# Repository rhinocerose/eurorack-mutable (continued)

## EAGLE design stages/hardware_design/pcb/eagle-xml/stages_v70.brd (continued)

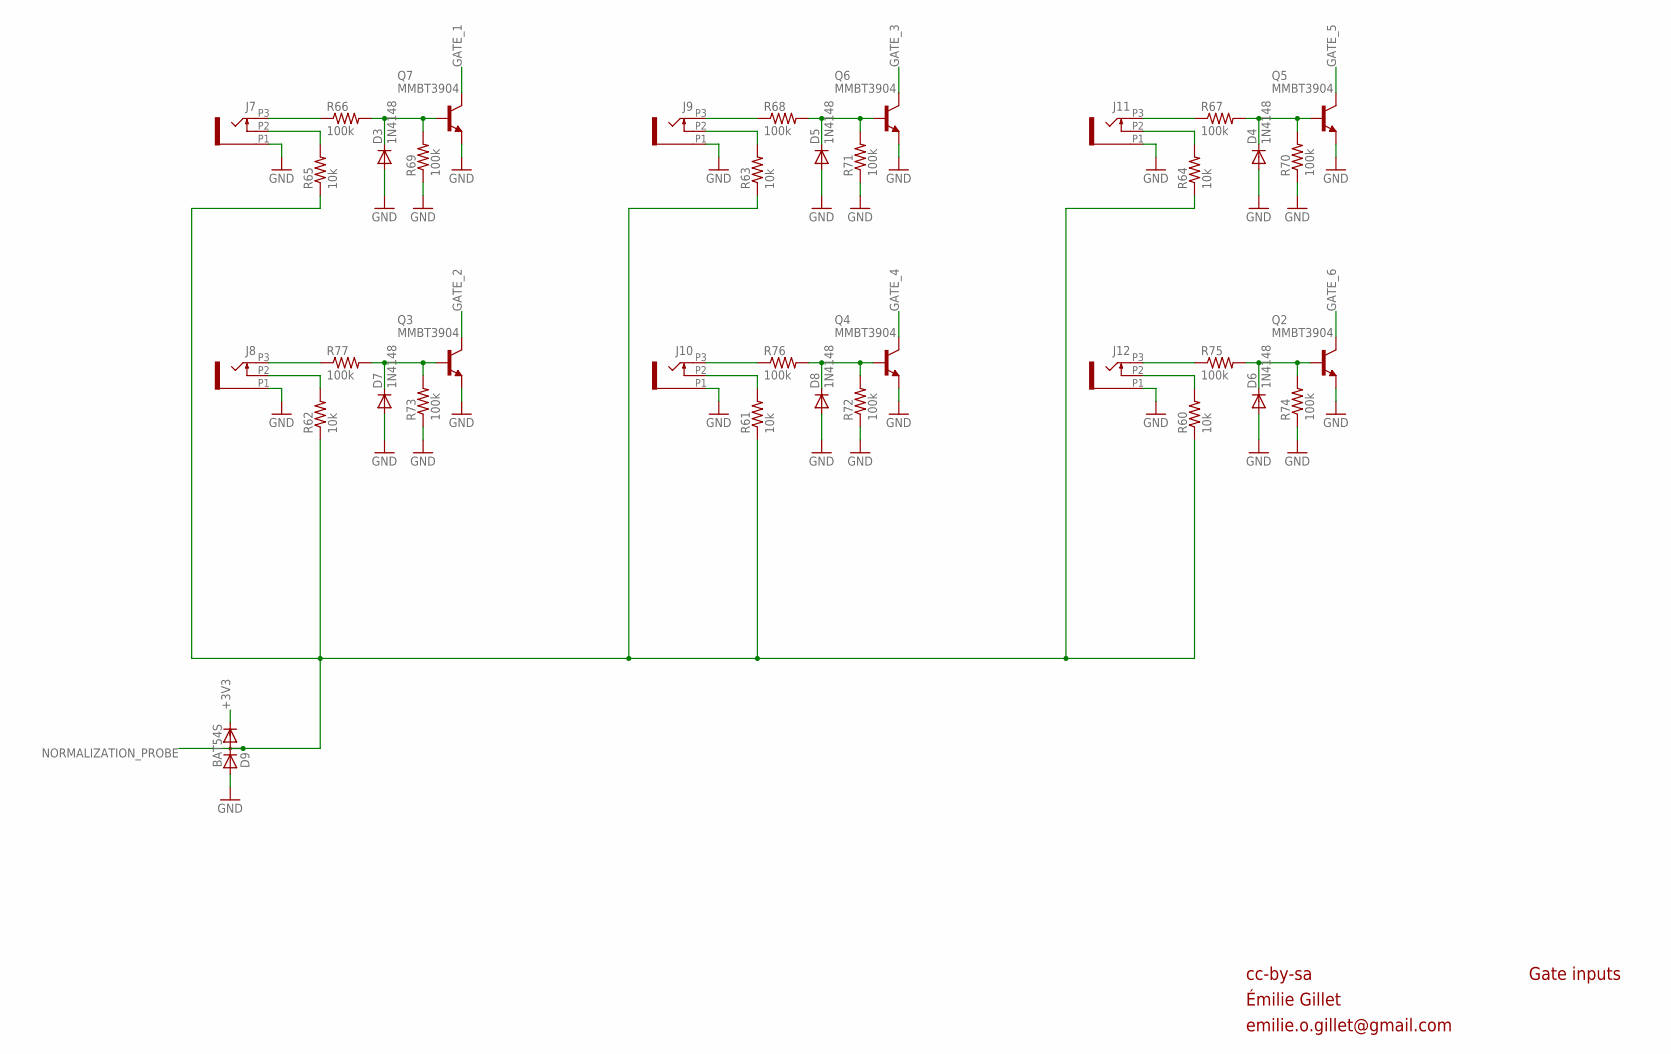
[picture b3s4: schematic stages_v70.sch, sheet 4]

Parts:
D3, D4, D5, D6, D7, D8: 1N4148; SOD523
D9: BAT54S; SOT23
J7, J8, J9, J10, J11, J12: PJ301_THONKICONN6; WQP_PJ_301M6
Q2, Q3, Q4, Q5, Q6, Q7: MMBT3904; SOT23-BEC
R60, R61, R62, R63, R64, R65: 10k; R0402
R66, R67, R68, R69, R70, R71, R72, R73, R74, R75, R76, R77: 100k; R0402

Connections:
+3V3: D9.2 (C); also elsewhere on the board
GATE_1: Q7.C; also elsewhere on the board
GATE_2: Q3.C; also elsewhere on the board
GATE_3: Q6.C; also elsewhere on the board
GATE_4: Q4.C; also elsewhere on the board
GATE_5: Q5.C; also elsewhere on the board
GATE_6: Q2.C; also elsewhere on the board
GND: D3.A, D4.A, D5.A, D6.A, D7.A, D8.A, D9.1 (A), J7.P1 (1), J8.P1 (1), J9.P1 (1), J10.P1 (1), J11.P1 (1), J12.P1 (1), Q2.E, Q3.E, Q4.E, Q5.E, Q6.E, Q7.E, R69.1, R70.1, R71.1, R72.1, R73.1, R74.1; also elsewhere on the board
unnamed: J9.P3 (3), R68.1
unnamed: J10.P3 (3), R76.1
unnamed: J10.P2 (2), R61.2
unnamed: J9.P2 (2), R63.2
unnamed: D5.C, Q6.B, R68.2, R71.2
unnamed: D8.C, Q4.B, R72.2, R76.2
unnamed: J11.P3 (3), R67.1
unnamed: J12.P3 (3), R75.1
unnamed: J12.P2 (2), R60.2
unnamed: J11.P2 (2), R64.2
unnamed: D4.C, Q5.B, R67.2, R70.2
unnamed: D6.C, Q2.B, R74.2, R75.2
unnamed: J8.P3 (3), R77.1
unnamed: J8.P2 (2), R62.2
unnamed: J7.P2 (2), R65.2
unnamed: D3.C, Q7.B, R66.2, R69.2
unnamed: D7.C, Q3.B, R73.2, R77.2
unnamed: J7.P3 (3), R66.1
NORMALIZATION_PROBE: D9.3 (AC), R60.1, R61.1, R62.1, R63.1, R64.1, R65.1; also elsewhere on the board

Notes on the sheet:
cc-by-sa
Gate inputs
Émilie Gillet
emilie.o.gillet@gmail.com

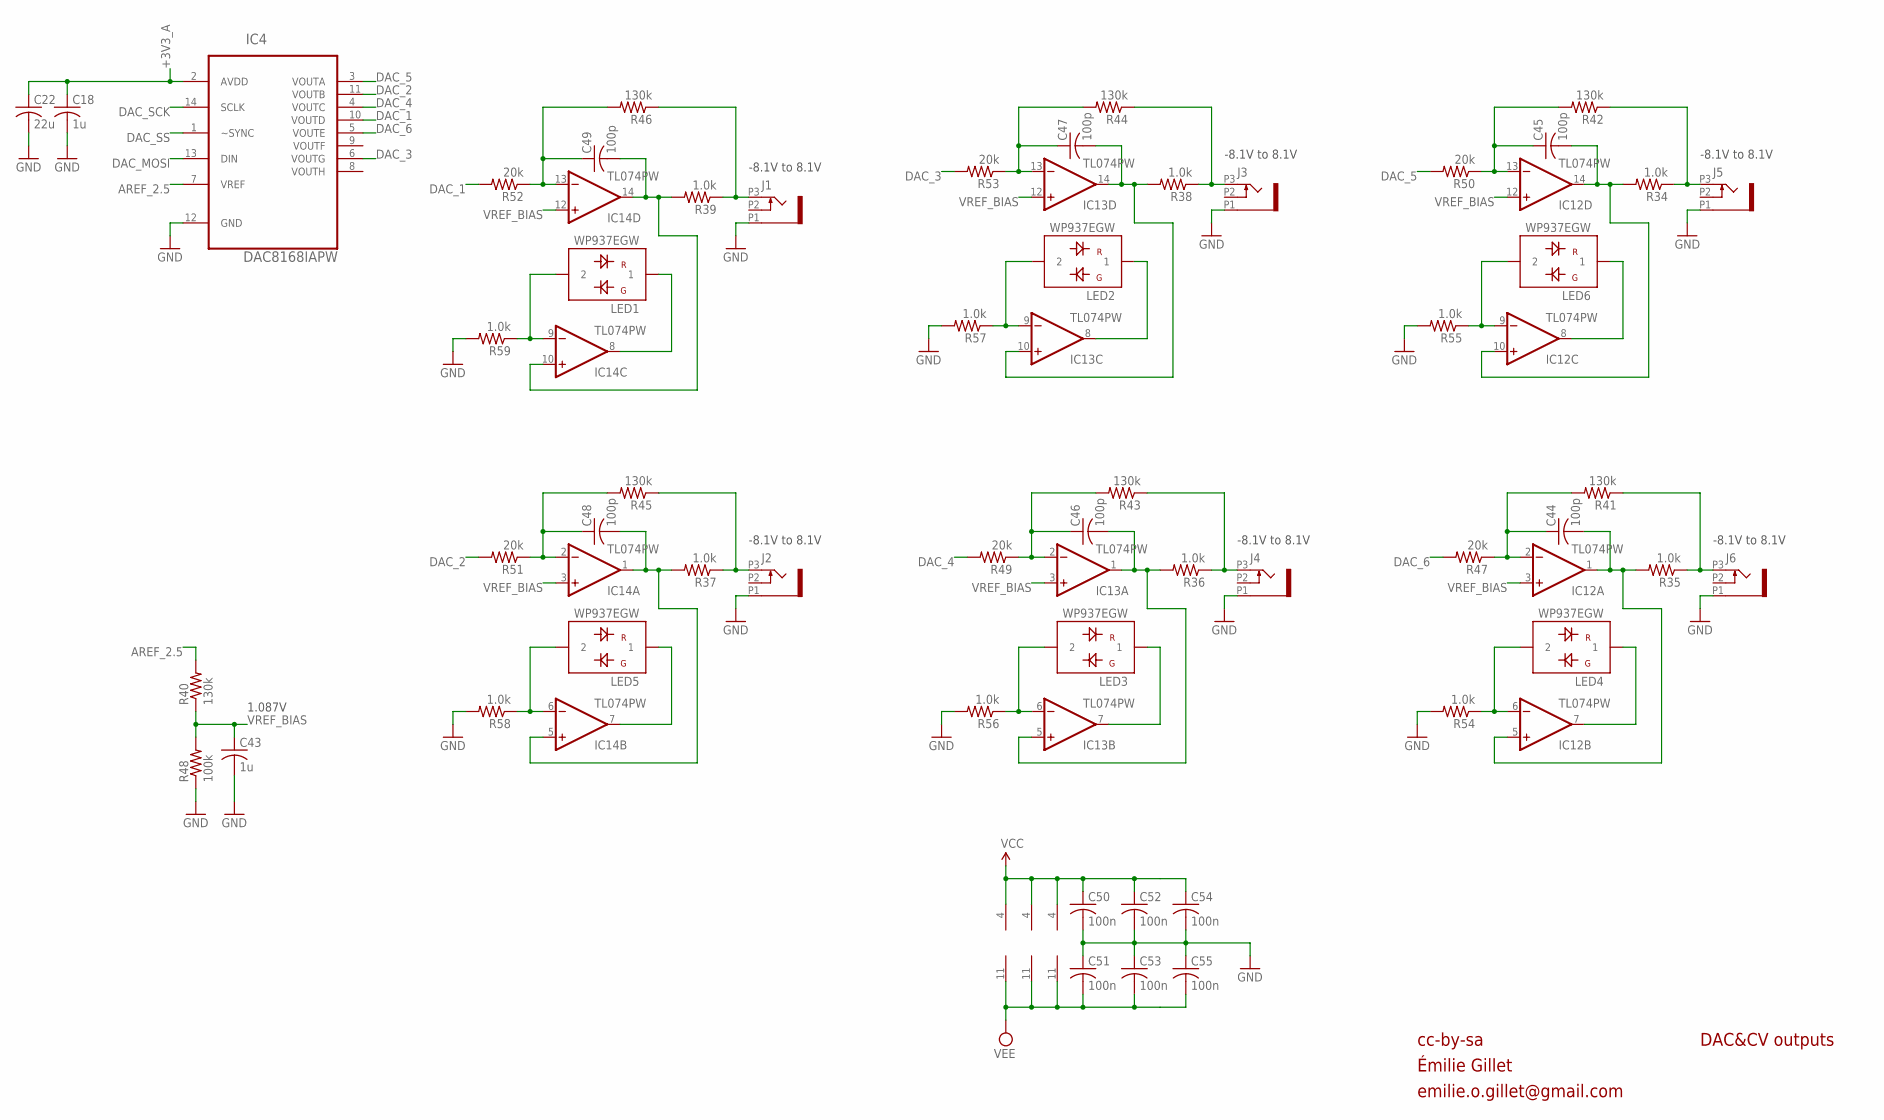
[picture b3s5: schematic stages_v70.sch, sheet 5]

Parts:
C18, C43: 1u; C0402
C22: 22u; C1206
C44, C45, C46, C47, C48, C49: 100p; C0402
C50, C51, C52, C53, C54, C55: 100n; C0402
IC4: DAC8168IAPW; RPDSOG14
IC12, IC13, IC14: TL074PW; TSSOP14_065
J1, J2, J3, J4, J5, J6: PJ301_THONKICONN6; WQP_PJ_301M6
LED1, LED2, LED3, LED4, LED5, LED6: WP937EGW; LED3MM
R34, R35, R36, R37, R38, R39: 1.0k; R0603
R40, R41, R42, R43, R44, R45, R46: 130k; R0402
R47, R49, R50, R51, R52, R53: 20k; R0402
R48: 100k; R0402
R54, R55, R56, R57, R58, R59: 1.0k; R0402

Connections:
+3V3_A: C18.1, C22.1, IC4.2 (AVDD); also elsewhere on the board
AREF_2.5: IC4.7 (VREF), R40.2
DAC_1: IC4.10 (VOUTD), R52.2
DAC_2: IC4.11 (VOUTB), R51.2
DAC_3: IC4.6 (VOUTG), R53.2
DAC_4: IC4.4 (VOUTC), R49.2
DAC_5: IC4.3 (VOUTA), R50.2
DAC_6: IC4.5 (VOUTE), R47.2
DAC_MOSI: IC4.13 (DIN); also elsewhere on the board
DAC_SCK: IC4.14 (SCLK); also elsewhere on the board
DAC_SS: IC4.1 (~SYNC); also elsewhere on the board
GND: C18.2, C22.2, C43.2, C50.2, C51.1, C52.2, C53.1, C54.2, C55.1, IC4.12 (GND), J1.P1 (1), J2.P1 (1), J3.P1 (1), J4.P1 (1), J5.P1 (1), J6.P1 (1), R48.1, R54.2, R55.2, R56.2, R57.2, R58.2, R59.2; also elsewhere on the board
unnamed: C49.2, IC14.10 (+IN), IC14.14 (OUT), R39.2
unnamed: J1.P3 (3), R39.1, R46.1
unnamed: J2.P3 (3), R37.1, R45.1
unnamed: J4.P3 (3), R36.1, R43.1
unnamed: C46.1, IC13.2 (-IN), R43.2, R49.1
unnamed: C48.1, IC14.2 (-IN), R45.2, R51.1
unnamed: C47.1, IC13.13 (-IN), R44.2, R53.1
unnamed: C49.1, IC14.13 (-IN), R46.2, R52.1
unnamed: J3.P3 (3), R38.1, R44.1
unnamed: IC14.9 (-IN), LED1.2, R59.1
unnamed: IC14.8 (OUT), LED1.1
unnamed: C47.2, IC13.10 (+IN), IC13.14 (OUT), R38.2
unnamed: IC13.9 (-IN), LED2.2, R57.1
unnamed: IC13.8 (OUT), LED2.1
unnamed: C48.2, IC14.1 (OUT), IC14.5 (+IN), R37.2
unnamed: IC14.6 (-IN), LED5.2, R58.1
unnamed: IC14.7 (OUT), LED5.1
unnamed: C46.2, IC13.1 (OUT), IC13.5 (+IN), R36.2
unnamed: IC13.6 (-IN), LED3.2, R56.1
unnamed: IC13.7 (OUT), LED3.1
unnamed: J6.P3 (3), R35.1, R41.1
unnamed: C44.1, IC12.2 (-IN), R41.2, R47.1
unnamed: C45.1, IC12.13 (-IN), R42.2, R50.1
unnamed: J5.P3 (3), R34.1, R42.1
unnamed: C45.2, IC12.10 (+IN), IC12.14 (OUT), R34.2
unnamed: IC12.9 (-IN), LED6.2, R55.1
unnamed: IC12.8 (OUT), LED6.1
unnamed: C44.2, IC12.1 (OUT), IC12.5 (+IN), R35.2
unnamed: IC12.6 (-IN), LED4.2, R54.1
unnamed: IC12.7 (OUT), LED4.1
VCC: C50.1, C52.1, C54.1, IC12.4 (V+), IC13.4 (V+), IC14.4 (V+); also elsewhere on the board
VEE: C51.2, C53.2, C55.2, IC12.11 (V-), IC13.11 (V-), IC14.11 (V-); also elsewhere on the board
VREF_BIAS: C43.1, IC12.3 (+IN), IC12.12 (+IN), IC13.3 (+IN), IC13.12 (+IN), IC14.3 (+IN), IC14.12 (+IN), R40.1, R48.2

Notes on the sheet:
cc-by-sa
DAC&CV outputs
-8.1V to 8.1V
1.087V
Émilie Gillet
emilie.o.gillet@gmail.com

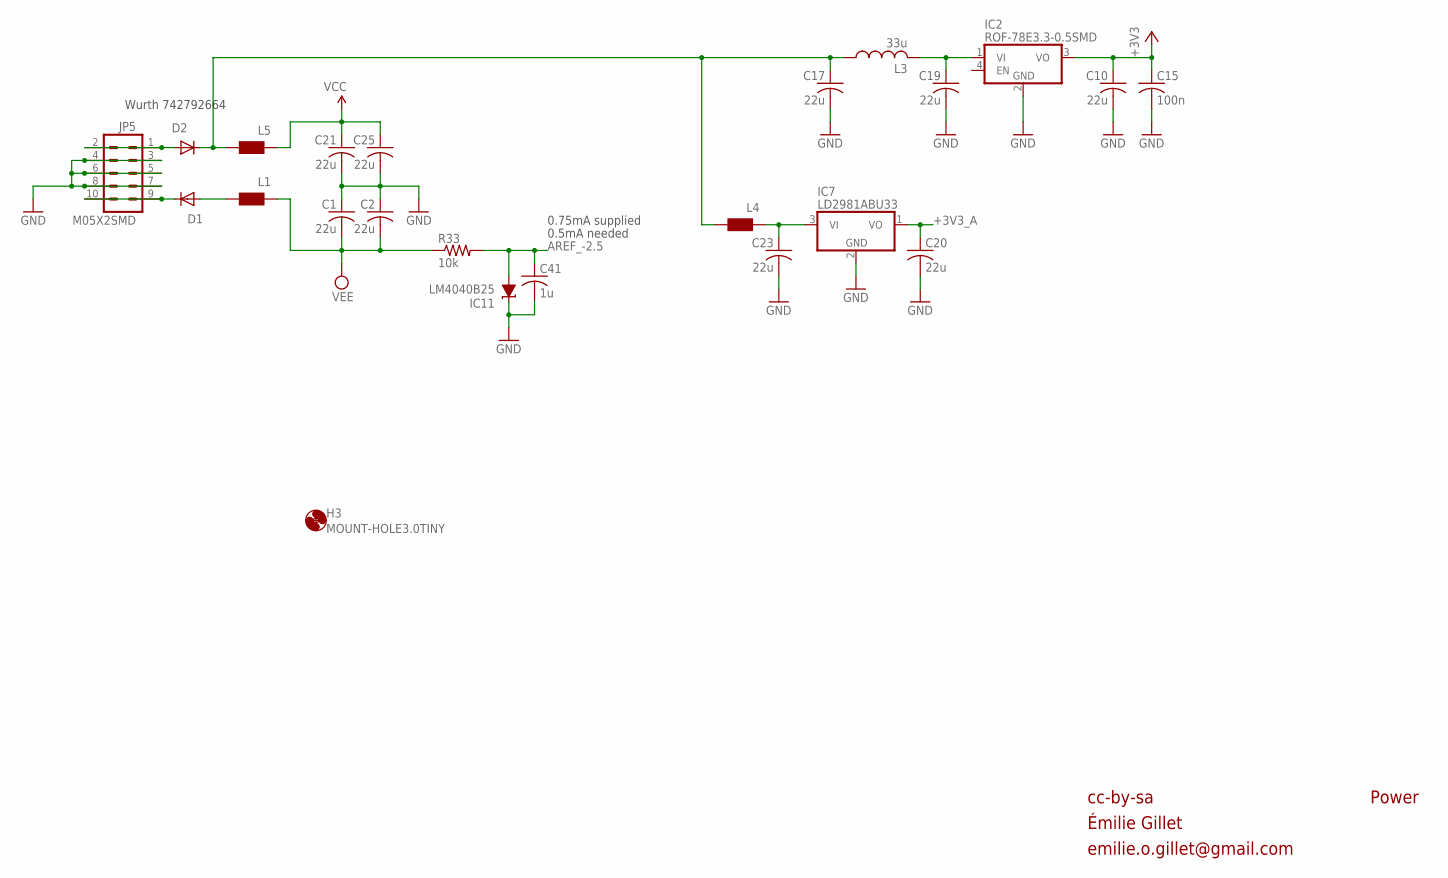
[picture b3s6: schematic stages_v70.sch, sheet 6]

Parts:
C1, C2, C10, C17, C19, C20, C21, C23, C25: 22u; C1206
C15: 100n; C0402
C41: 1u; C0402
D1, D2: 1N5819HW; SOD123
H3: MOUNT-HOLE3.0TINY; 3,0TINY
IC2: ROF-78E3.3-0.5SMD; ROF78EXX-0.5SMD
IC7: LD2981ABU33; SOT89
IC11: LM4040B25; DBZ_R-PDSO-G3
JP5: M05X2SMD; 2X5-SMD
L1, L4, L5: WE-CBF_0603; 0603
L3: 33u; L2012C
R33: 10k; R0402

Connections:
+3V3: C10.1, C15.1, IC2.3 (VO); also elsewhere on the board
+3V3_A: C20.1, IC7.1 (VO); also elsewhere on the board
AREF_-2.5: C41.1, IC11.2 (A), R33.2; also elsewhere on the board
GND: C1.1, C2.1, C10.2, C15.2, C17.2, C19.2, C20.2, C21.2, C23.2, C25.2, C41.2, IC2.2 (GND), IC7.2 (GND), IC11.1 (C), JP5.3, JP5.4, JP5.5, JP5.6, JP5.7, JP5.8; also elsewhere on the board
unnamed: D2.A, JP5.1, JP5.2
unnamed: D1.A, L1.2
unnamed: C23.1, IC7.3 (VI), L4.1
unnamed: C17.1, D2.C, L3.1, L4.2, L5.2
unnamed: D1.C, JP5.9, JP5.10
unnamed: C19.1, IC2.1 (VI), L3.2
VCC: C21.1, C25.1, L5.1; also elsewhere on the board
VEE: C1.2, C2.2, L1.1, R33.1; also elsewhere on the board

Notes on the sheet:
0.5mA needed
Wurth 742792664
0.75mA supplied
cc-by-sa
Power
Émilie Gillet
emilie.o.gillet@gmail.com

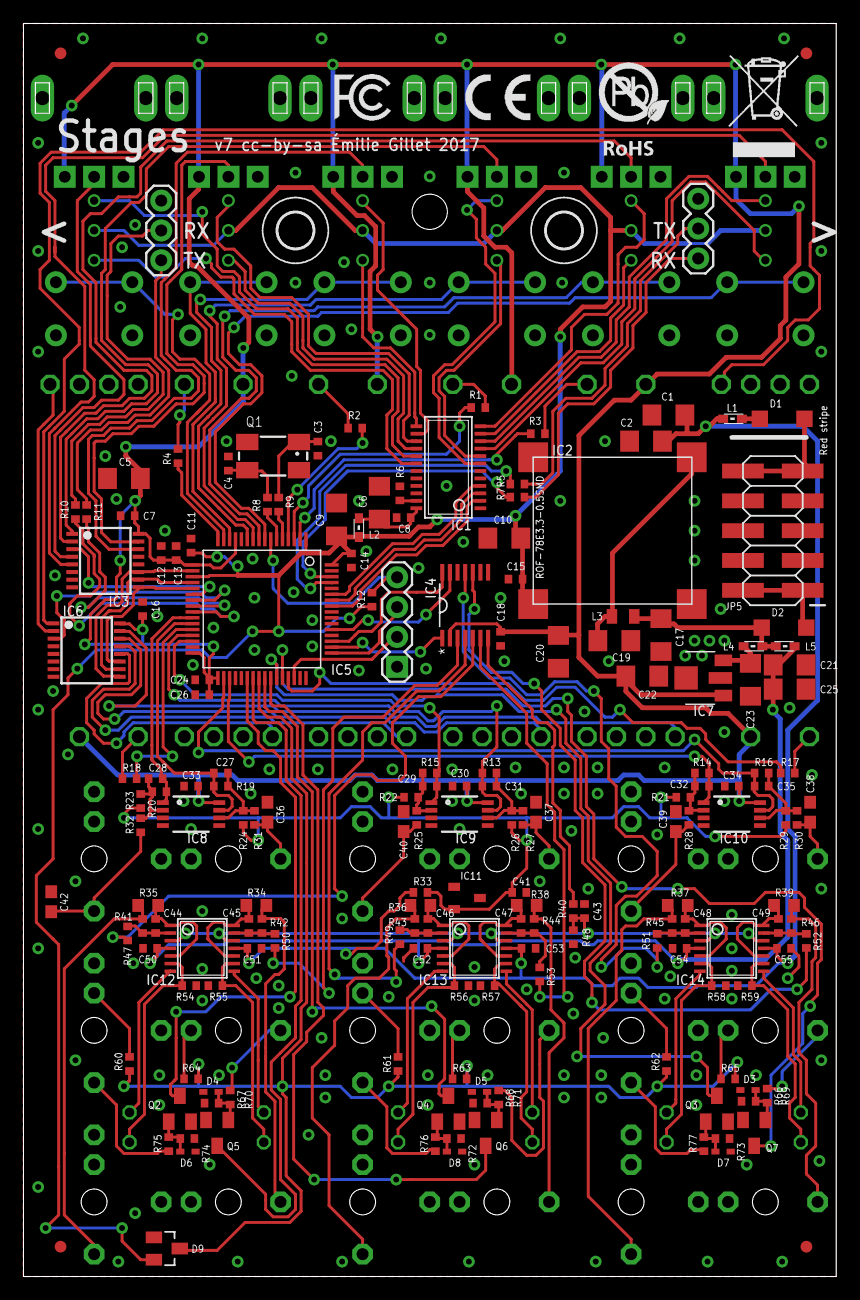
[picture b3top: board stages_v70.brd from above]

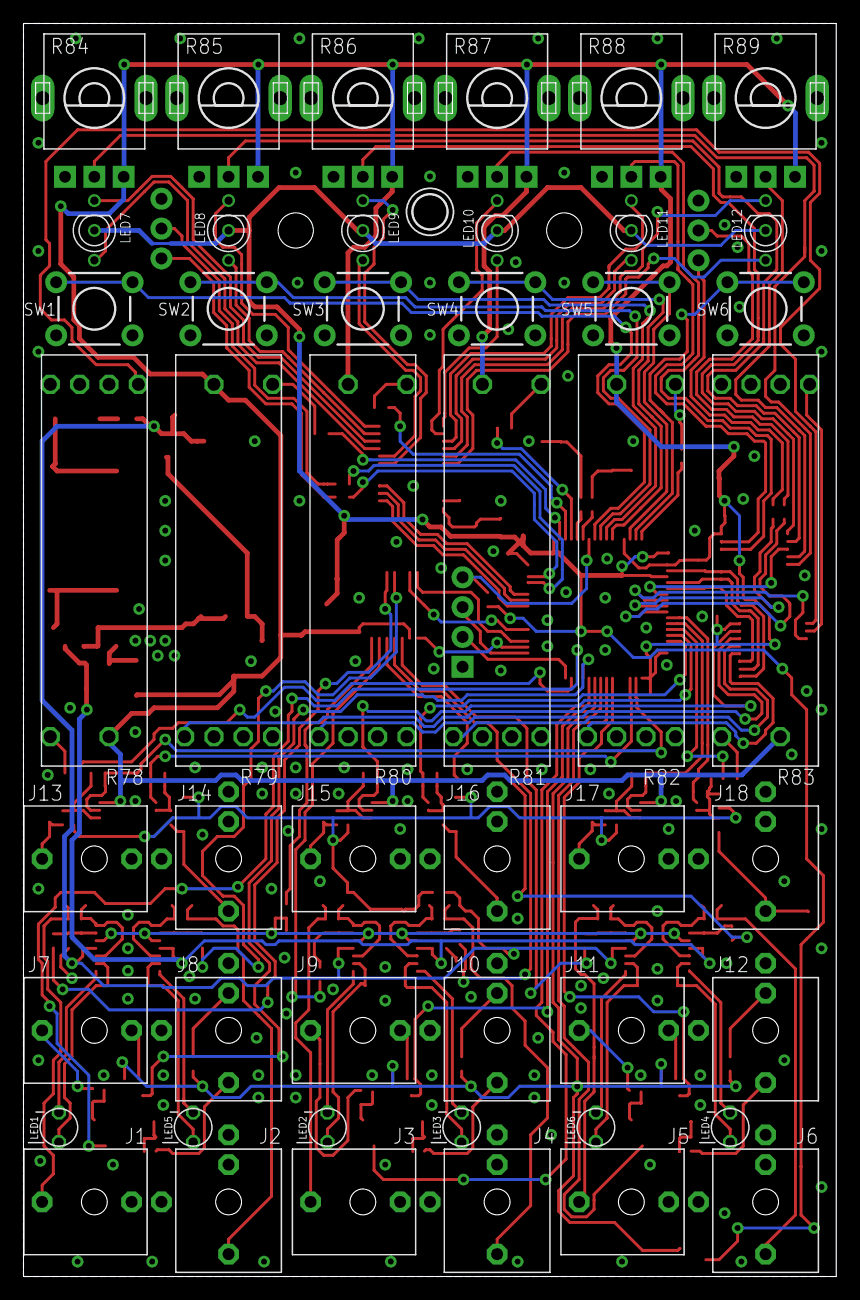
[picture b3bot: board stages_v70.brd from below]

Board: 2 copper layers, 69.2 x 106.7 mm, 230 parts (49 on the bottom side), 163 nets.

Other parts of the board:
U$1: ROHS
U$2: ROHS_2
U$3: FCC_SMALL
U$4: CE_SMALL

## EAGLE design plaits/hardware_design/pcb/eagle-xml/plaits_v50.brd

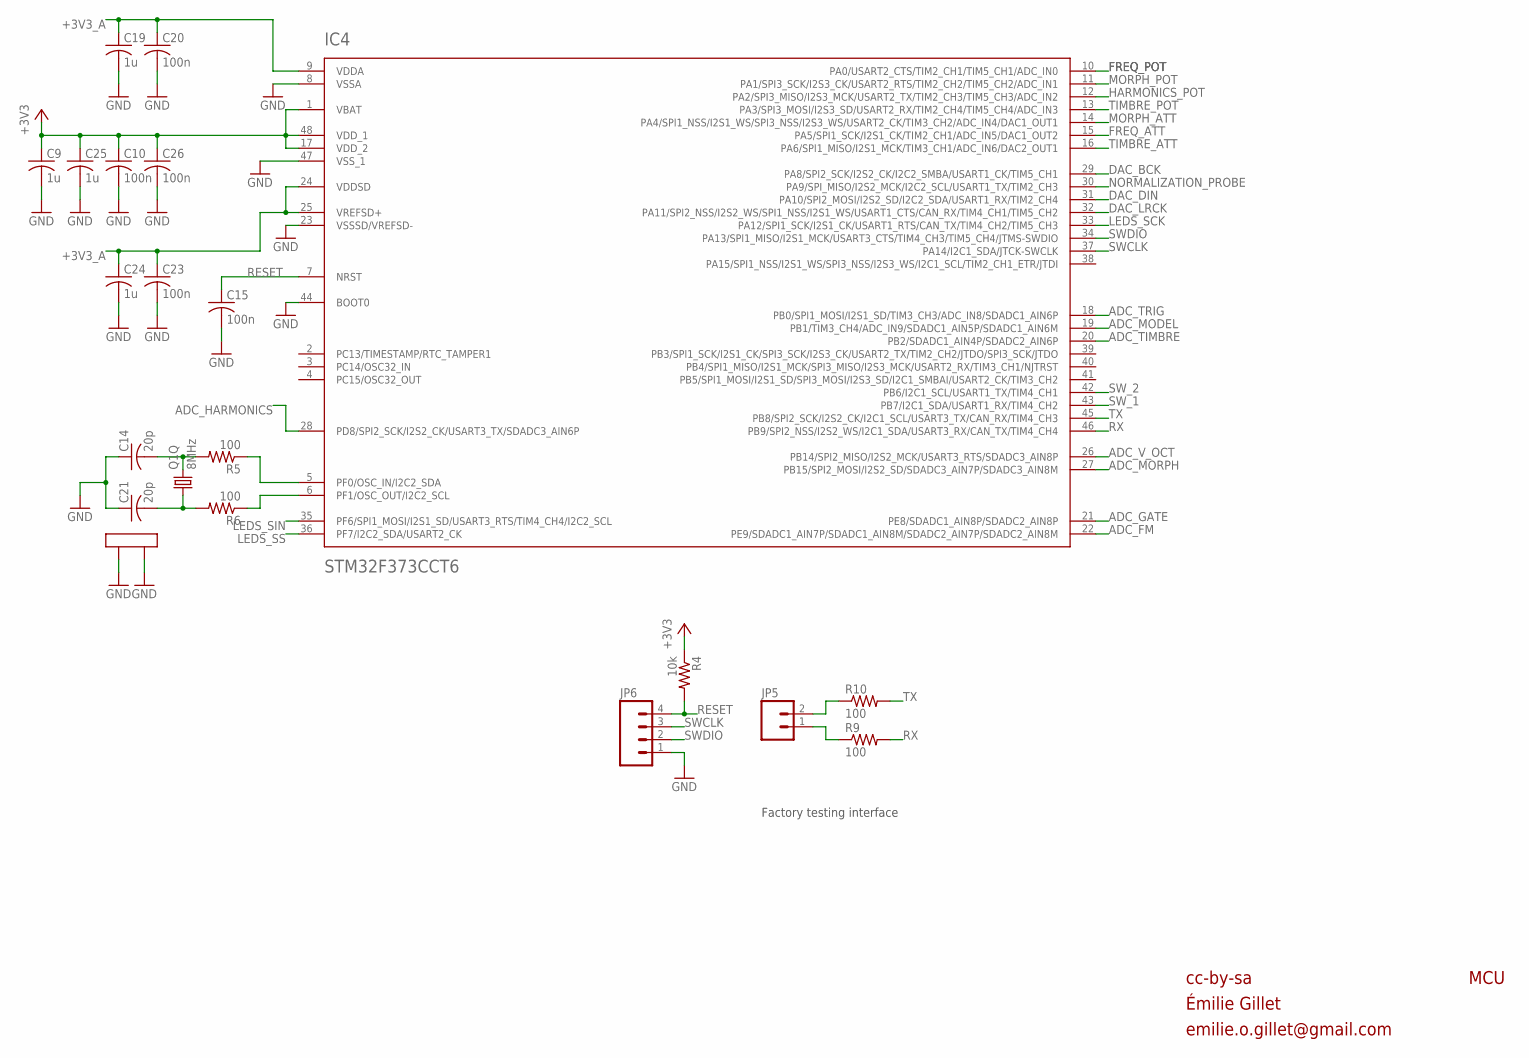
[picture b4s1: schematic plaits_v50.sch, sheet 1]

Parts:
C9, C19, C24, C25: 1u; C0402
C10, C15, C20, C23, C26: 100n; C0402
C14, C21: 20p; C0402
IC4: STM32F373CCT6; LQFP48
JP5: M02PTH; 1X02
JP6: M04PTH; 1X04
Q1: 8MHz; CTS406
R4: 10k; R0402
R5, R6, R9, R10: 100; R0402

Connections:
+3V3: C9.1, C10.1, C25.1, C26.1, IC4.1 (VBAT), IC4.17 (VDD_2), IC4.48 (VDD_1), R4.1; also elsewhere on the board
+3V3_A: C19.1, C20.1, C23.1, C24.1, IC4.9 (VDDA), IC4.24 (VDDSD), IC4.25 (VREFSD+); also elsewhere on the board
ADC_FM: IC4.22 (PE9/SDADC1_AIN7P/SDADC1_AIN8M/SDADC2_AI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); also elsewhere on the board
ADC_GATE: IC4.21 (PE8/SDADC1_AIN8P/SDADC2_AIN8P); also elsewhere on the board
ADC_HARMONICS: IC4.28 (PD8/SPI2_SCK/I2S2_CK/USART3_TX/SDADC3_A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); also elsewhere on the board
ADC_MODEL: IC4.19 (PB1/TIM3_CH4/ADC_IN9/SDADC1_AIN5P/SDADC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); also elsewhere on the board
ADC_MORPH: IC4.27 (PB15/SPI2_MOSI/I2S2_SD/SDADC3_AIN7P/SDA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); also elsewhere on the board
ADC_TIMBRE: IC4.20 (PB2/SDADC1_AIN4P/SDADC2_AIN6P); also elsewhere on the board
ADC_TRIG: IC4.18 (PB0/SPI1_MOSI/I2S1_SD/TIM3_CH3/ADC_IN8/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); also elsewhere on the board
ADC_V_OCT: IC4.26 (PB14/SPI2_MISO/I2S2_MCK/USART3_RTS/SDAD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); also elsewhere on the board
DAC_BCK: IC4.29 (PA8/SPI2_SCK/I2S2_CK/I2C2_SMBA/USART1_C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); also elsewhere on the board
DAC_DIN: IC4.31 (PA10/SPI2_MOSI/I2S2_SD/I2C2_SDA/USART1_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); also elsewhere on the board
DAC_LRCK: IC4.32 (PA11/SPI2_NSS/I2S2_WS/SPI1_NSS/I2S1_WS/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); also elsewhere on the board
FREQ_ATT: IC4.15 (PA5/SPI1_SCK/I2S1_CK/TIM2_CH1/ADC_IN5/D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); also elsewhere on the board
FREQ_POT: IC4.10 (PA0/USART2_CTS/TIM2_CH1/TIM5_CH1/ADC_IN0); also elsewhere on the board
GND: C9.2, C10.2, C14.1, C15.2, C19.2, C20.2, C21.1, C23.2, C24.2, C25.2, C26.2, IC4.8 (VSSA), IC4.23 (VSSSD/VREFSD-), IC4.44 (BOOT0), IC4.47 (VSS_1), JP6.1, Q1.2 (LID1), Q1.4 (LID2); also elsewhere on the board
HARMONICS_POT: IC4.12 (PA2/SPI3_MISO/I2S3_MCK/USART2_TX/TIM2_C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); also elsewhere on the board
LEDS_SCK: IC4.33 (PA12/SPI1_SCK/I2S1_CK/USART1_RTS/CAN_TX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); also elsewhere on the board
LEDS_SIN: IC4.35 (PF6/SPI1_MOSI/I2S1_SD/USART3_RTS/TIM4_C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); also elsewhere on the board
LEDS_SS: IC4.36 (PF7/I2C2_SDA/USART2_CK); also elsewhere on the board
MORPH_ATT: IC4.14 (PA4/SPI1_NSS/I2S1_WS/SPI3_NSS/I2S3_WS/U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); also elsewhere on the board
MORPH_POT: IC4.11 (PA1/SPI3_SCK/I2S3_CK/USART2_RTS/TIM2_CH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); also elsewhere on the board
unnamed: IC4.5 (PF0/OSC_IN/I2C2_SDA), R5.1
unnamed: IC4.6 (PF1/OSC_OUT/I2C2_SCL), R6.1
unnamed: C14.2, Q1.3 (2), R5.2
unnamed: JP5.2, R10.1
unnamed: C21.2, Q1.1, R6.2
unnamed: JP5.1, R9.1
NORMALIZATION_PROBE: IC4.30 (PA9/SPI_MISO/I2S2_MCK/I2C2_SCL/USART1_T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); also elsewhere on the board
RESET: C15.1, IC4.7 (NRST), JP6.4, R4.2
RX: IC4.46 (PB9/SPI2_NSS/I2S2_WS/I2C1_SDA/USART3_RX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), R9.2
SWCLK: IC4.37 (PA14/I2C1_SDA/JTCK-SWCLK), JP6.3
SWDIO: IC4.34 (PA13/SPI1_MISO/I2S1_MCK/USART3_CTS/TIM4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), JP6.2
SW_1: IC4.43 (PB7/I2C1_SDA/USART1_RX/TIM4_CH2); also elsewhere on the board
SW_2: IC4.42 (PB6/I2C1_SCL/USART1_TX/TIM4_CH1); also elsewhere on the board
TIMBRE_ATT: IC4.16 (PA6/SPI1_MISO/I2S1_MCK/TIM3_CH1/ADC_IN6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); also elsewhere on the board
TIMBRE_POT: IC4.13 (PA3/SPI3_MOSI/I2S3_SD/USART2_RX/TIM2_CH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); also elsewhere on the board
TX: IC4.45 (PB8/SPI2_SCK/I2S2_CK/I2C1_SCL/USART3_TX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), R10.2

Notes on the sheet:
cc-by-sa
MCU
Factory testing interface
Émilie Gillet
emilie.o.gillet@gmail.com

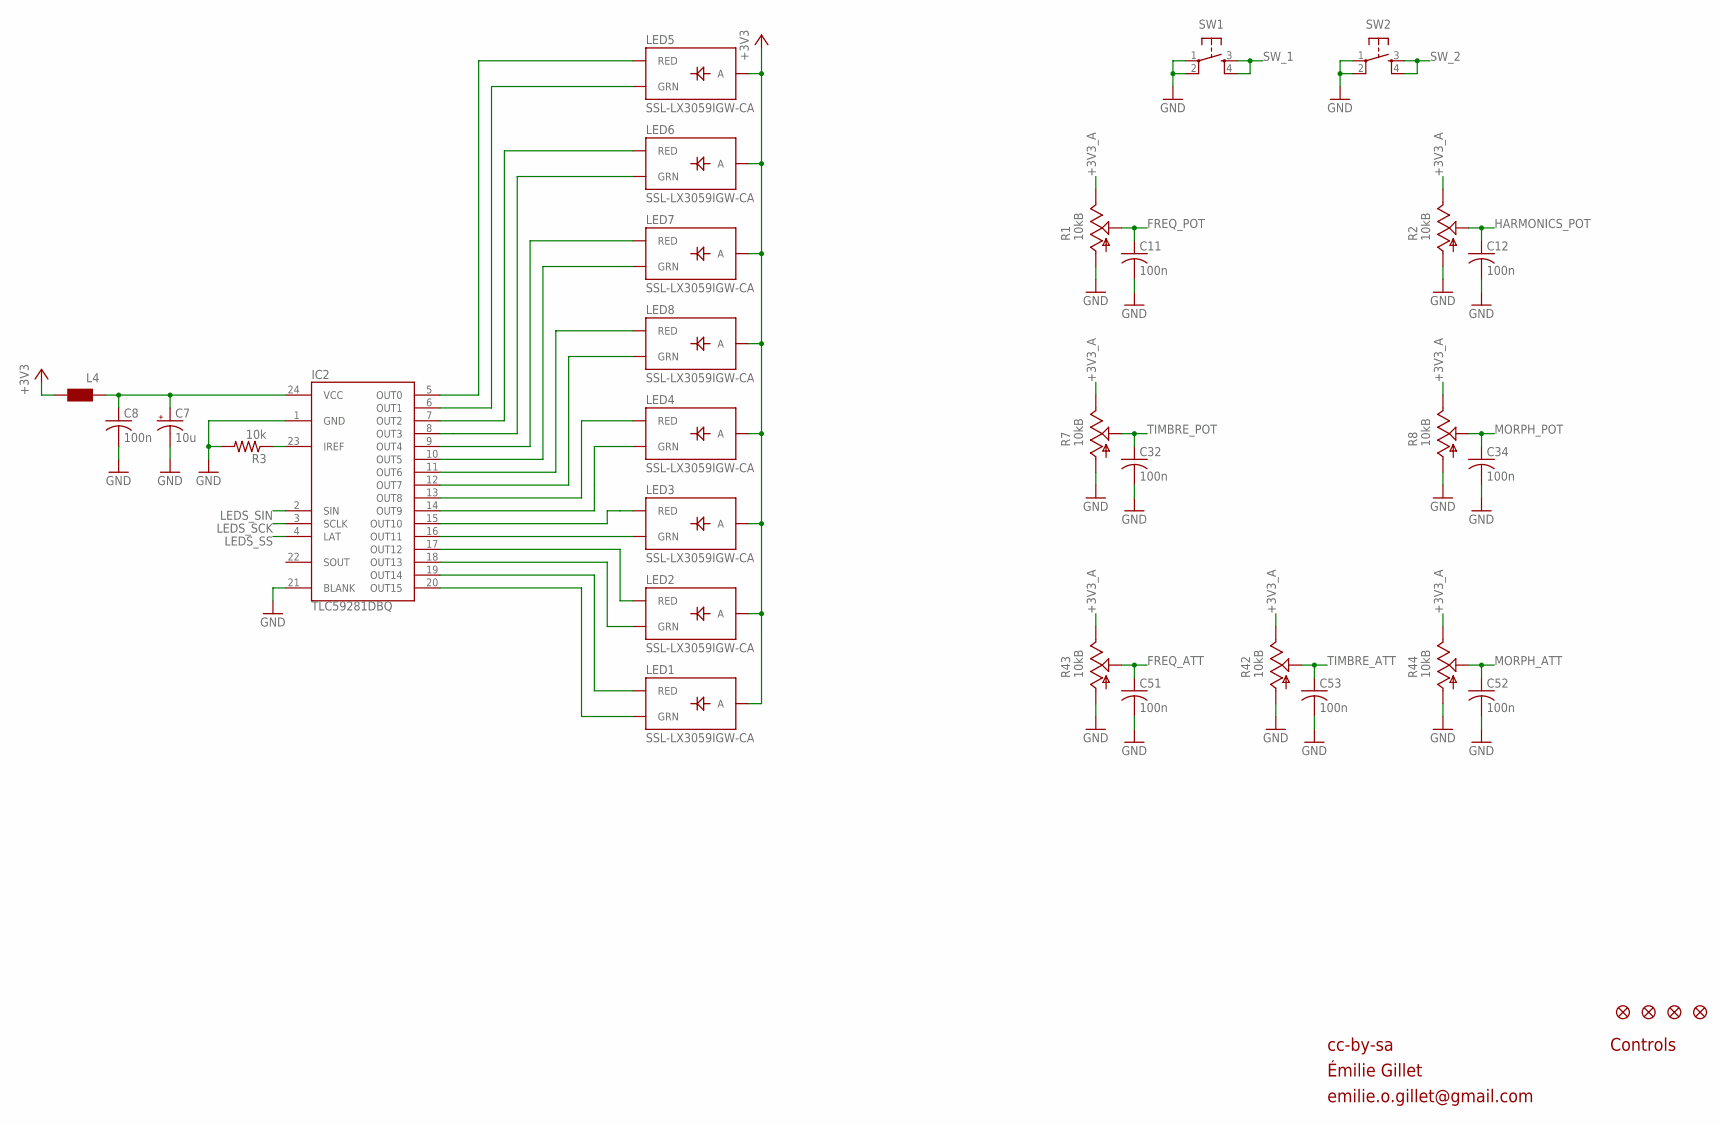
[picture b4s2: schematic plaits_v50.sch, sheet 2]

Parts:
C7: 10u; PANASONIC_A
C8, C11, C12, C32, C34, C51, C52, C53: 100n; C0402
IC2: TLC59281DBQ; TSSOP24_0635
JP1, JP2, JP3, JP4: FIDUCIAL1X2; FIDUCIAL-1X2
L4: WE-CBF_0603; 0603
LED1, LED2, LED3, LED4, LED5, LED6, LED7, LED8: SSL-LX3059IGW-CA; LED-BICOLOR-THROUGHHOLE-LUMEX
R1, R2, R7, R8: 10kB; ALPS_POT_VERTICAL_PS
R3: 10k; R0402
R42, R43, R44: 10kB; ALPS_POT_VERTICAL
SW1, SW2: TAC_SWITCHPTH; TACTILE-PTH

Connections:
+3V3: L4.2, LED1.A, LED2.A, LED3.A, LED4.A, LED5.A, LED6.A, LED7.A, LED8.A; also elsewhere on the board
+3V3_A: R1.P$1 (E), R2.P$1 (E), R7.P$1 (E), R8.P$1 (E), R42.P$1 (E), R43.P$1 (E), R44.P$1 (E); also elsewhere on the board
FREQ_ATT: C51.1, R43.P$2 (S); also elsewhere on the board
FREQ_POT: C11.1, R1.P$2 (S); also elsewhere on the board
GND: C7.-, C8.2, C11.2, C12.2, C32.2, C34.2, C51.2, C52.2, C53.2, IC2.1 (GND), IC2.21 (BLANK), R1.P$3 (A), R2.P$3 (A), R3.2, R7.P$3 (A), R8.P$3 (A), R42.P$3 (A), R43.P$3 (A), R44.P$3 (A), SW1.1, SW1.2, SW2.1, SW2.2; also elsewhere on the board
HARMONICS_POT: C12.1, R2.P$2 (S); also elsewhere on the board
LEDS_SCK: IC2.3 (SCLK); also elsewhere on the board
LEDS_SIN: IC2.2 (SIN); also elsewhere on the board
LEDS_SS: IC2.4 (LAT); also elsewhere on the board
MORPH_ATT: C52.1, R44.P$2 (S); also elsewhere on the board
MORPH_POT: C34.1, R8.P$2 (S); also elsewhere on the board
unnamed: IC2.12 (OUT7), LED8.GREEN_C (GRN)
unnamed: IC2.11 (OUT6), LED8.RED_C (RED)
unnamed: IC2.10 (OUT5), LED7.GREEN_C (GRN)
unnamed: IC2.9 (OUT4), LED7.RED_C (RED)
unnamed: IC2.8 (OUT3), LED6.GREEN_C (GRN)
unnamed: IC2.13 (OUT8), LED4.RED_C (RED)
unnamed: IC2.7 (OUT2), LED6.RED_C (RED)
unnamed: IC2.14 (OUT9), LED4.GREEN_C (GRN)
unnamed: IC2.6 (OUT1), LED5.GREEN_C (GRN)
unnamed: IC2.15 (OUT10), LED3.RED_C (RED)
unnamed: IC2.16 (OUT11), LED3.GREEN_C (GRN)
unnamed: IC2.17 (OUT12), LED2.RED_C (RED)
unnamed: IC2.18 (OUT13), LED2.GREEN_C (GRN)
unnamed: IC2.19 (OUT14), LED1.RED_C (RED)
unnamed: IC2.5 (OUT0), LED5.RED_C (RED)
unnamed: IC2.20 (OUT15), LED1.GREEN_C (GRN)
unnamed: C7.+, C8.1, IC2.24 (VCC), L4.1
unnamed: IC2.23 (IREF), R3.1
SW_1: SW1.3, SW1.4; also elsewhere on the board
SW_2: SW2.3, SW2.4; also elsewhere on the board
TIMBRE_ATT: C53.1, R42.P$2 (S); also elsewhere on the board
TIMBRE_POT: C32.1, R7.P$2 (S); also elsewhere on the board

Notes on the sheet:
cc-by-sa
Controls
Émilie Gillet
emilie.o.gillet@gmail.com

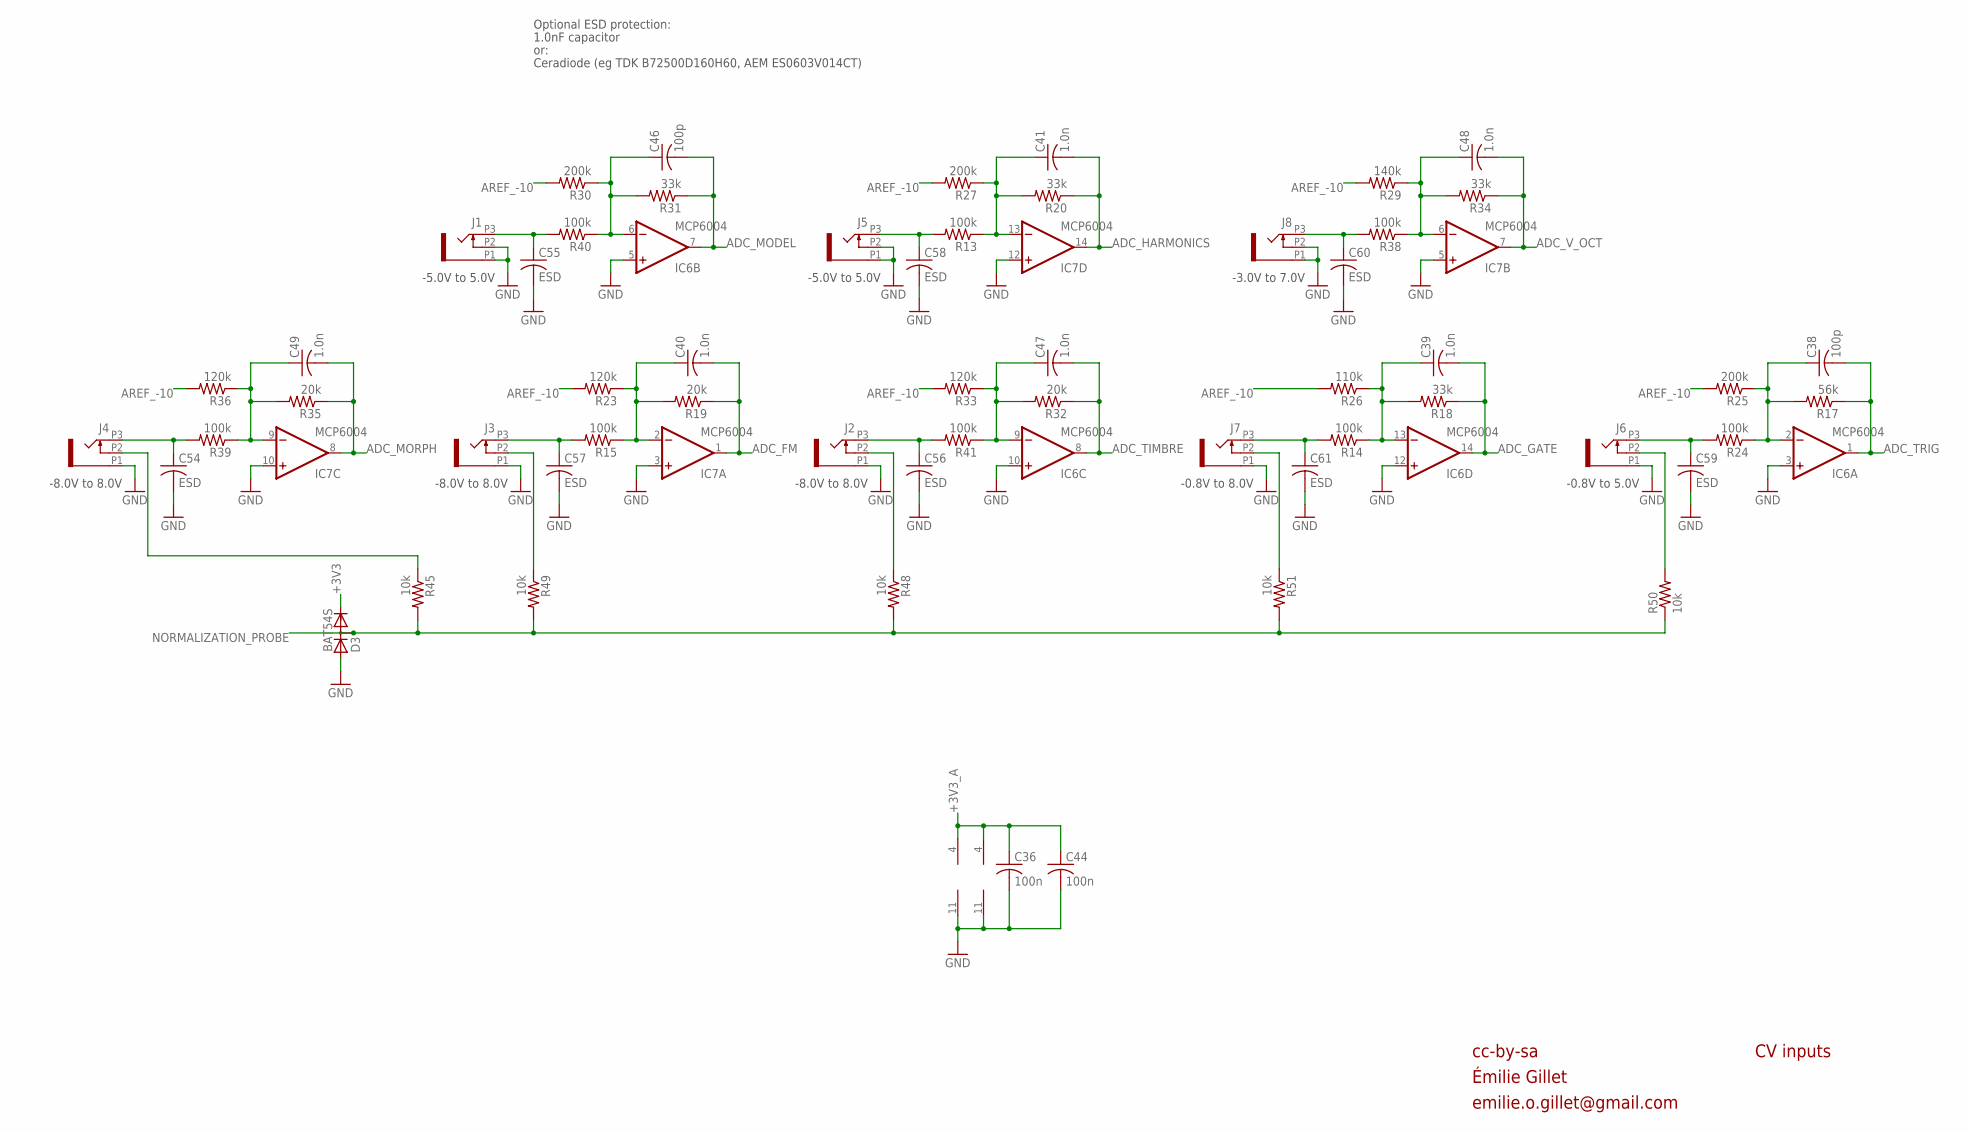
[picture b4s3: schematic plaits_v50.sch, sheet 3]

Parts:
C36, C44: 100n; C0402
C38, C46: 100p; C0402
C39, C40, C41, C47, C48, C49: 1.0n; C0402
C54, C55, C56, C57, C58, C59, C60, C61: ESD; C0603
D3: BAT54S; SOT23
IC6, IC7: MCP6004; TSSOP14_065
J1, J2, J3, J4, J5, J6, J7, J8: PJ301_THONKICONN6; WQP_PJ_301M6
R13, R14, R15, R24, R38, R39, R40, R41: 100k; R0402
R17: 56k; R0402
R18, R20, R31, R34: 33k; R0402
R19, R32, R35: 20k; R0402
R23, R33, R36: 120k; R0402
R25, R27, R30: 200k; R0402
R26: 110k; R0402
R29: 140k; R0402
R45, R48, R49, R50, R51: 10k; R0402

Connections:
+3V3: D3.2 (C); also elsewhere on the board
+3V3_A: C36.1, C44.1, IC6.4 (V+), IC7.4 (V+); also elsewhere on the board
ADC_FM: C40.2, IC7.1 (OUT), R19.1; also elsewhere on the board
ADC_GATE: C39.2, IC6.14 (OUT), R18.1; also elsewhere on the board
ADC_HARMONICS: C41.2, IC7.14 (OUT), R20.1; also elsewhere on the board
ADC_MODEL: C46.2, IC6.7 (OUT), R31.1; also elsewhere on the board
ADC_MORPH: C49.2, IC7.8 (OUT), R35.1; also elsewhere on the board
ADC_TIMBRE: C47.2, IC6.8 (OUT), R32.1; also elsewhere on the board
ADC_TRIG: C38.2, IC6.1 (OUT), R17.1; also elsewhere on the board
ADC_V_OCT: C48.2, IC7.7 (OUT), R34.1; also elsewhere on the board
AREF_-10: R23.2, R25.2, R26.2, R27.2, R29.2, R30.2, R33.2, R36.2; also elsewhere on the board
FM_IN: C57.1, J3.P3 (3), R15.2
GATE_IN: C61.1, J7.P3 (3), R14.2
GATE_IN1: C59.1, J6.P3 (3), R24.2
GND: C36.2, C44.2, C54.2, C55.2, C56.2, C57.2, C58.2, C59.2, C60.2, C61.2, D3.1 (A), IC6.3 (+IN), IC6.5 (+IN), IC6.10 (+IN), IC6.11 (V-), IC6.12 (+IN), IC7.3 (+IN), IC7.5 (+IN), IC7.10 (+IN), IC7.11 (V-), IC7.12 (+IN), J1.P1 (1), J1.P2 (2), J2.P1 (1), J3.P1 (1), J4.P1 (1), J5.P1 (1), J5.P2 (2), J6.P1 (1), J7.P1 (1), J8.P1 (1), J8.P2 (2); also elsewhere on the board
HARMONICS_IN: C58.1, J5.P3 (3), R13.2
MODEL_IN: C55.1, J1.P3 (3), R40.2
MORPH_IN: C54.1, J4.P3 (3), R39.2
unnamed: J6.P2 (2), R50.2
unnamed: C38.1, IC6.2 (-IN), R17.2, R24.1, R25.1
unnamed: J3.P2 (2), R49.1
unnamed: J2.P2 (2), R48.1
unnamed: J4.P2 (2), R45.1
unnamed: C39.1, IC6.13 (-IN), R14.1, R18.2, R26.1
unnamed: C48.1, IC7.6 (-IN), R29.1, R34.2, R38.1
unnamed: C56.1, J2.P3 (3), R41.2
unnamed: C49.1, IC7.9 (-IN), R35.2, R36.1, R39.1
unnamed: C40.1, IC7.2 (-IN), R15.1, R19.2, R23.1
unnamed: J7.P2 (2), R51.1
unnamed: C46.1, IC6.6 (-IN), R30.1, R31.2, R40.1
unnamed: C47.1, IC6.9 (-IN), R32.2, R33.1, R41.1
unnamed: C41.1, IC7.13 (-IN), R13.1, R20.2, R27.1
NORMALIZATION_PROBE: D3.3 (AC), R45.2, R48.2, R49.2, R50.1, R51.2; also elsewhere on the board
V_OCT_IN: C60.1, J8.P3 (3), R38.2

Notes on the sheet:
cc-by-sa
CV inputs
-3.0V to 7.0V
-8.0V to 8.0V
-5.0V to 5.0V
-0.8V to 8.0V
-0.8V to 5.0V
Optional ESD protection:
1.0nF capacitor
or:
Ceradiode (eg TDK B72500D160H60, AEM ES0603V014CT)
Émilie Gillet
emilie.o.gillet@gmail.com
